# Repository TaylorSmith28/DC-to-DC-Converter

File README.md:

# DC-to-DC-Converter
## Overview

This is a DC-to-DC Converter Design for Walla Walla University's Power Electronics Course. The goal of this project was to create a 12-15V to 5V DC converter in order to be able to charge a phone from a voltage source ranging from 12-15V. Shown above is the block diagram with the general design of our converter. 
## Design Specifications
1. Takes a 12-15V input and outputs a 5V up to 3A
2. Is able to charge both Android Devices as well as Iphones
3. Board size is to be 10cm by 10cm
4. Efficieny of 80% or above
5. Cost less than $25
## Schematic

Shown above is ou final schematic for our project. Our input is delived from a 12-15V source to the screw terminal. For our final version we used a set of 8 AA batteries to generate 12V into the screw terminal. The input then passes a ferrite bead in order to limit noise coming from the input. It then passes into a LM25765-5 Buck Converter. The LM25765 works as a simple switcher in conjuction with our inductor and schottky diode in order to create an average duty cyle of 5V. This 5V is then passed into a voltage divider, to get 2 and 2.5 V in order to use the data pins on the USB output. From the USB 5V are generated with a current ranging from about 20-30mA.

Shown here is the voltage divider used to power the data pins. The data pins had to be given a 2.75V on the D+ pin and 2V on the D-.
## PCB Design

Shown above is the PCB design. For our design we choose to make all our components through hole in order to make building, testing, and debugging easily approachable.
## Simulations

Shown above is the simulation of the voltage response of our DC-to-DC converter under load. We used the WEBENCH tool from Texas Instruments for our simulations. The simulation is limited by its time frame but the time frame cannot be adjusted to show further. It does demonstrate the duty cycle of the circuit. 
## Board Build Up Plan
1.	Take inventory of all parts
2.	Determine Correct Values for Components
3.	Inspect PCB for defects
4.	Solder Parts to board
a.	Use one board until it works or there is an error impending continued work on that board.
b.	Use KiCAD’s HTML BOM feature in order to assist with building the board
5.	Check board amperage.
6.	Test output voltage by inputting power from DC Power Supply.
7.	Use load resistor to test output voltage.
8.	Solder Battery Pack to Terminal Screw Input
9.	Use a charge doctor and a phone to connect and test output voltage and current
10.	Should having a working board at this point. 
## Results

These images show the results we obtained when the board was built and tested by use a 8 AA battery back for its input source and then connected to an IPhone charger. Also shown is the back side of the board where we attached our resistor divider. This allowed for the IPhone to be charged, while an Android device could have worked without the data pins. We did achieve a 5V output, and we observed a 20-30mA current to our phone. The reason for this current may be due to loss charge of in the batteries over testing.

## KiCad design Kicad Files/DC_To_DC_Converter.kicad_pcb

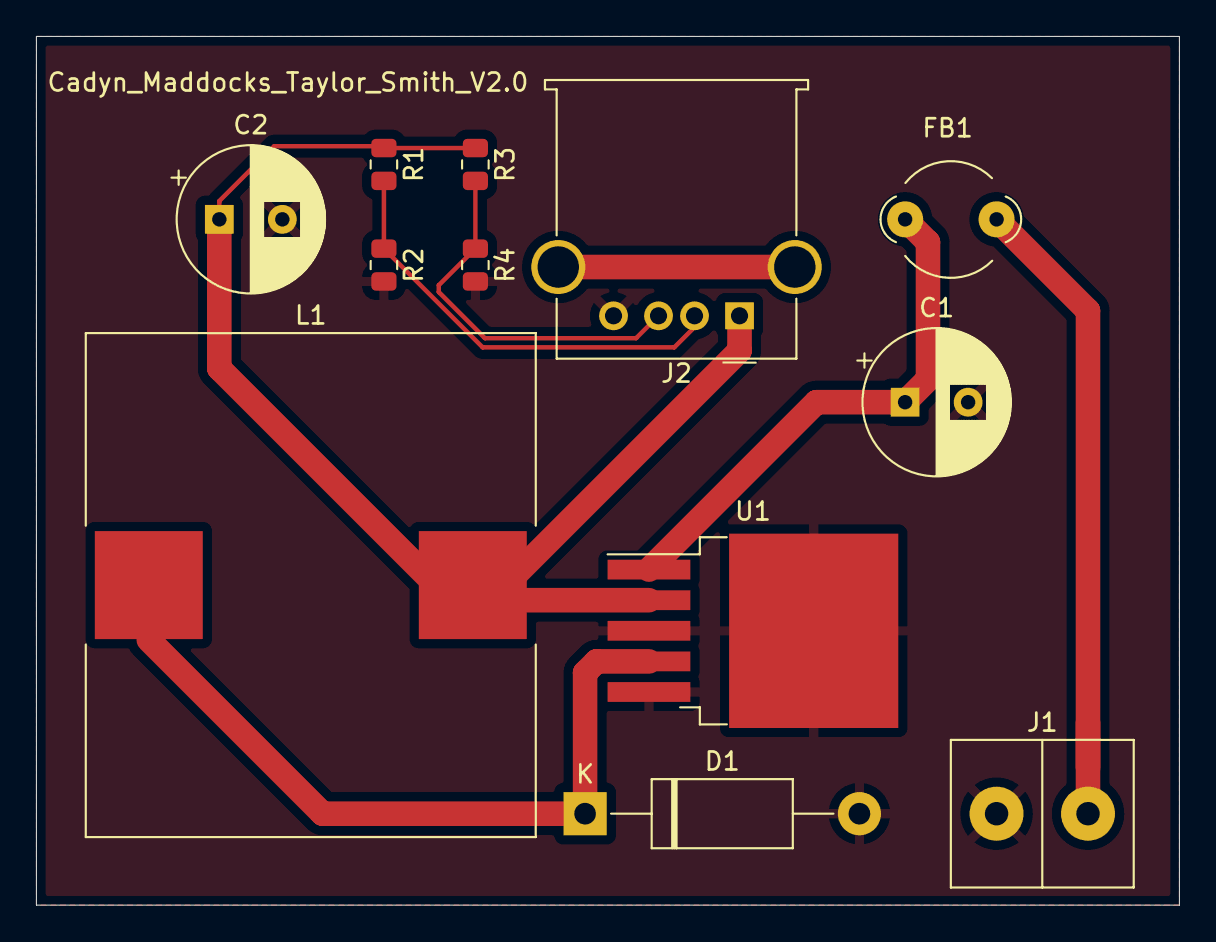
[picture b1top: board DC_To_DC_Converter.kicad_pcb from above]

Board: 2 copper layers, 63.5 x 48.3 mm, 12 parts (0 on the bottom side), 7 nets.

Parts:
C1: 120uF; CP_Radial_D8.0mm_P3.50mm
C2: 470uF; CP_Radial_D8.0mm_P3.50mm
D1: D_Schottky; D_DO-15_P15.24mm_Horizontal
FB1: FerriteBead; LairdTech_28C0236-0JW-10
J1: Screw_Terminal_01x02; 2 Pin TB006-508 Terminal Block
J2: USB_A; USB_A_Molex_67643_Horizontal
L1: 100uH; L_28x25mm_H20.5mm
R1: 130k; R_0805_2012Metric
R2: 160k; R_0805_2012Metric
R3: 150K; R_0805_2012Metric
R4: 100k; R_0805_2012Metric
U1: LM2576S-5; TO-263-5_TabPin3

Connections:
/2.75V: J2.2 (D-), R1.2, R2.1
/2V: J2.3 (D+), R3.2, R4.1
/5V: C2.1, J2.1 (VBUS), L1.2, R1.1, R3.1, U1.2 (OUT)
GND: C1.2, C2.2, D1.2 (A), J1.2, J2.4 (GND), R2.2, R4.2, U1.3 (GND), U1.5 (~ON/OFF)
unnamed: C1.1, FB1.2, U1.1 (VIN)
unnamed: D1.1 (K), L1.1, U1.4 (FB)
unnamed: FB1.1, J1.1

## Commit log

2022-06-08 2nd Commit
2022-06-08 Result Pictures
2022-06-08 Final Schematics
2022-06-09 Adding Block Diagram to Readme
2022-06-09 Adding Updated Schematic
